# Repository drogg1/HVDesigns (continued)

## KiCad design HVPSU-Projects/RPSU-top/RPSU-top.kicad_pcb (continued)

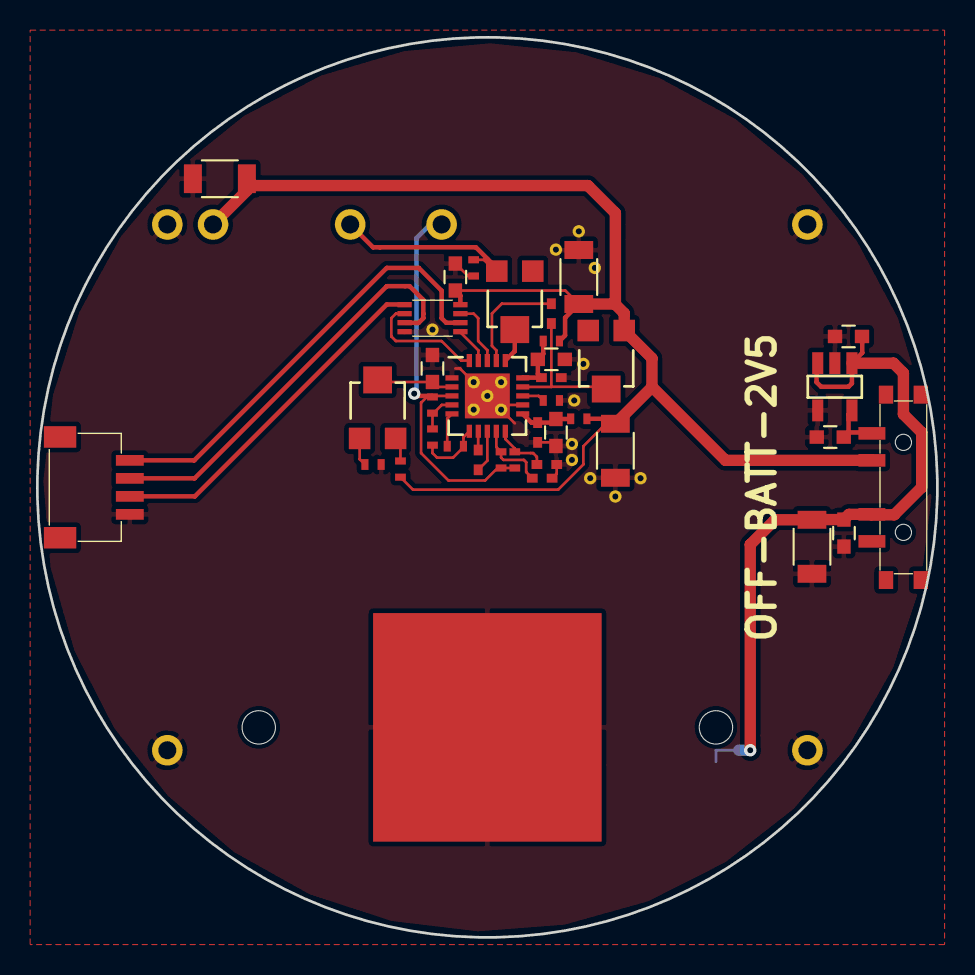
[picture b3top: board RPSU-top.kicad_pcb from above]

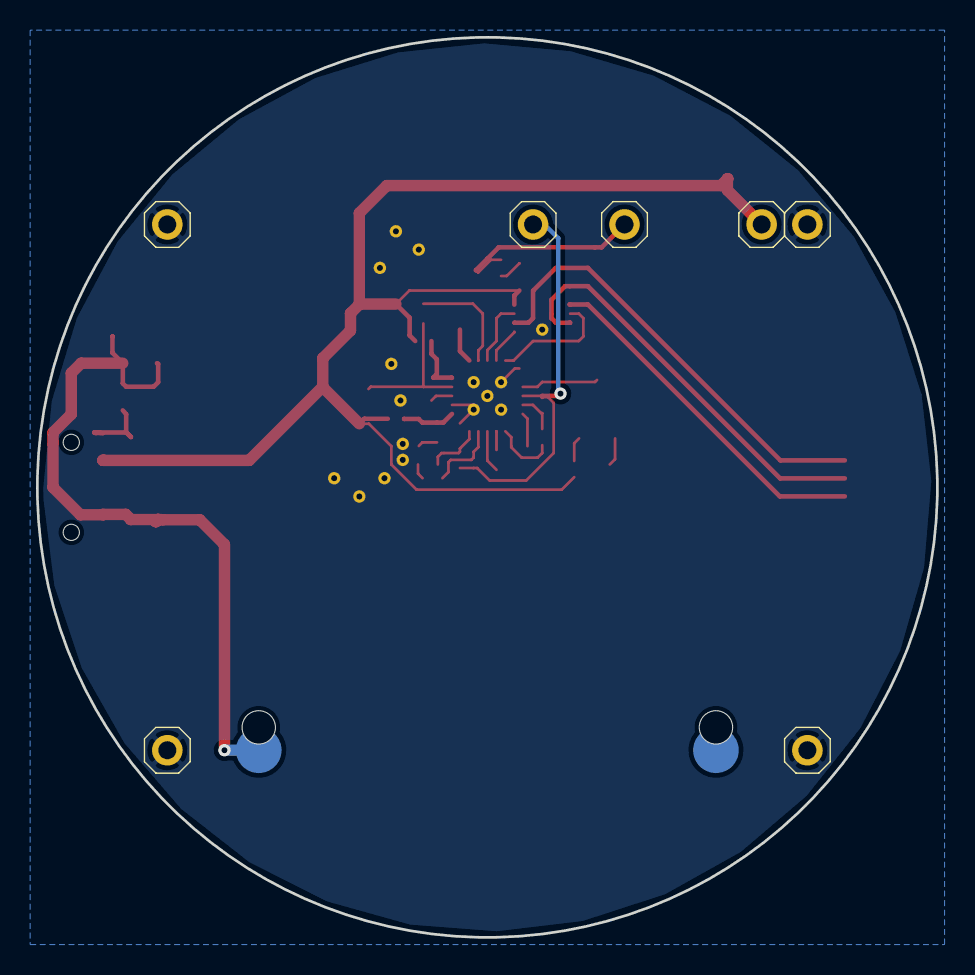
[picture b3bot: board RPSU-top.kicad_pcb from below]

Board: 2 copper layers, 50.0 x 50.0 mm, 44 parts (7 on the bottom side), 28 nets.

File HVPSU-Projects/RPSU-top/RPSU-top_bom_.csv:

Component,Description,Part,References,Value,Footprint,Quantity Per PCB,Datasheet
1,,Battery,BT1,Battery,KEY1027-ND-rev2,1,
2,Unpolarized capacitor,C_Small,C52 C54 C56 C58,0.1uF,C_0402_NoSilk,4,
3,Unpolarized capacitor,C_Small,C1 C63 C64 C65,10uF,C_1206,4,
4,Unpolarized capacitor,C_Small,C57,1nF,C_0402_NoSilk,1,
5,Unpolarized capacitor,C_Small,C50 C51 C53 C59 C60 C61 C62,1uF,C_0603,7,
6,Unpolarized capacitor,C_Small,C55,3.3nF,C_0402_NoSilk,1,
7,Connector 01x01,CONN_01X01,P2 P3 P4 P5 P6 P7 P8,CONN_01X01,PHS1x01_Pitch2.54mm_1D1.7P,7,
8,Connector 01x04,CONN_01X04,P1,CONN_01X04,SM04B-SRSS-TB(LF)(SN),1,
9,Resistor,R,R16 R17,10,R_0402_NoSilk,2,
10,Resistor,R,R1 R18 R19 R20 R22 R23,1M,R_0402_NoSilk,6,
11,Resistor,R,R15,2M,R_0402_NoSilk,1,
12,Resistor,R,R21,33M,R_0402_NoSilk,1,
13,Resistor,R,R14,560k,R_0402_NoSilk,1,
14,,POT-RESCUE-RPSU-top,RV1,1M,EVM3Y-POT,1,
15,,POT-RESCUE-RPSU-top,RV2 RV3,20k,EVM3Y-POT,2,
16,"3 position switch, SP3T",SP3T,SW1,SP3T,PCM13SMTR,1,
17,,SN74AUP3G17,U2,SN74AUP3G17,8-VFSOP,1,
18,,TPS78225DDCR,U3,TPS78225DDCR,TSOT-23-5,1,
19,,switch_ic4/5,U1,switch_ic4/5,QFN-20-1EP_4x4mm_Pitch0.5mm,1,





Component Groups:,19
Component Count:,44
Fitted Components:,44
Number of PCBs:,1
Total components:,44
Schematic Version:,
Schematic Date:,
BoM Date:,1/29/2019 10:01:43 PM
Schematic Source:,C:/Users/User/Google Drive/IC Research/Clean HV Designs/HVPSU-Projects/RPSU-top/RPSU-top.sch
KiCad Version:,Eeschema 4.0.2-stable

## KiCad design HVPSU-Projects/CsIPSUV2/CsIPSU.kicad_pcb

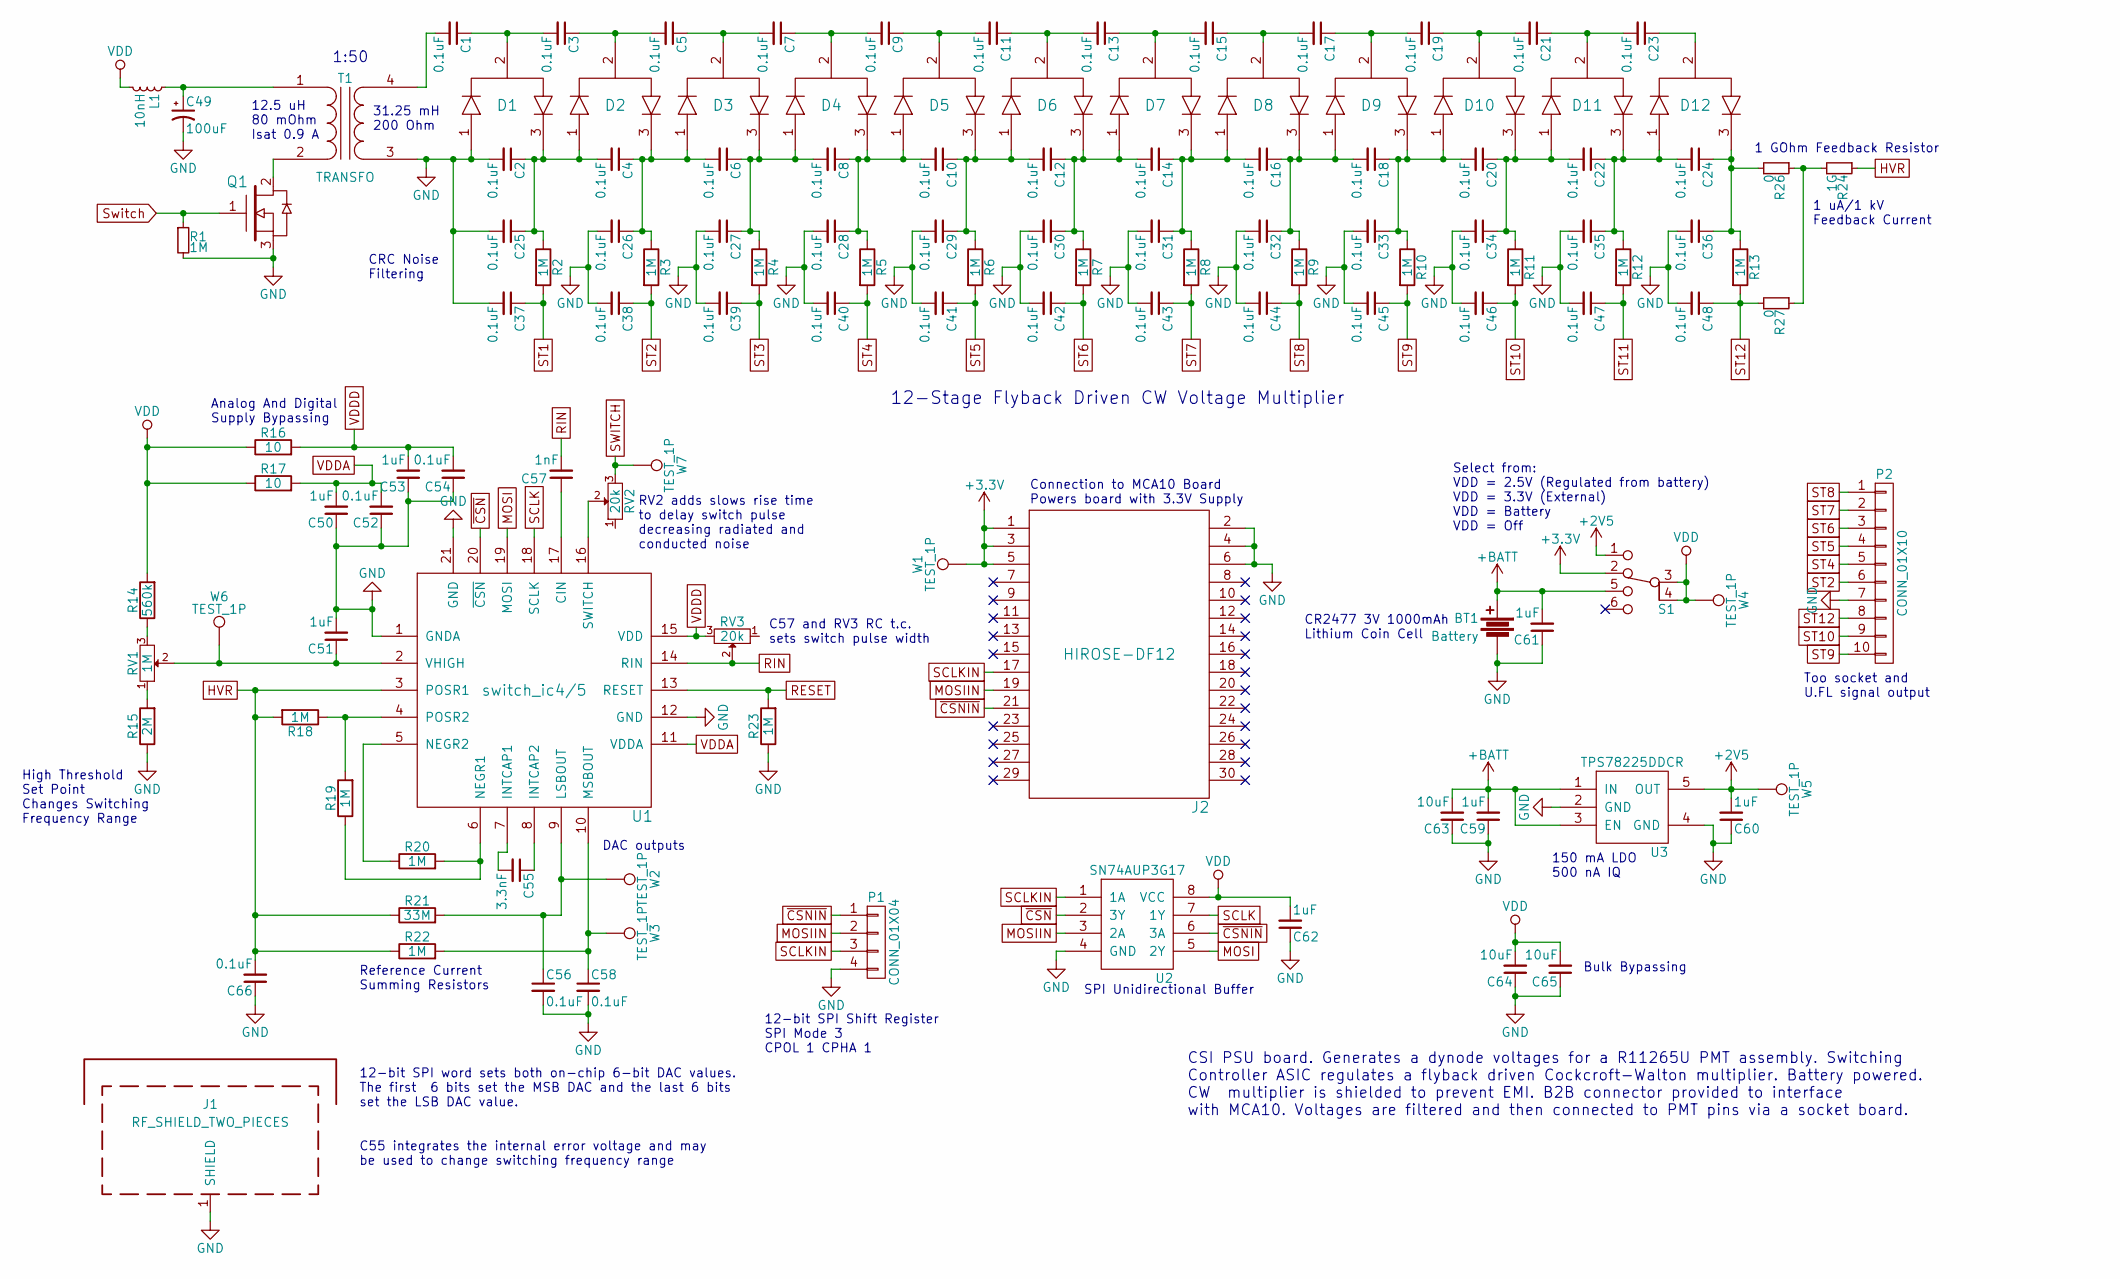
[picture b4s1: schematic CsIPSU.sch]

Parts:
BT1: Battery; KEY1027-ND
C1, C2, C3, C4, C5, C6, C7, C8, C9, C10, C11, C12, C13, C14, C15, C16, C17, C18, C19, C20, C21, C22, C23, C24: 0.1uF; HV-1206
C25, C26, C27, C28, C29, C30, C31, C32, C33, C34, C35, C36, C37, C38, C39, C40, C41, C42, C43, C44, C45, C46, C47, C48: 0.1uF; C_1812
C49: 100uF; CP_Tantalum_Case-C_EIA-6032-28_Reflow
C50, C51, C53, C59, C60, C61, C62: 1uF; C_0603
C52, C54, C56, C58, C66: 0.1uF; C_0402_NoSilk
C55: 3.3nF; C_0402_NoSilk
C57: 1nF; C_0402_NoSilk
C63, C64, C65: 10uF; C_1206
D1, D2, D3, D4, D5, D6, D7, D8, D9, D10, D11, D12: MMBD3004S; SOT23
J1: RF_SHIELD_TWO_PIECES; Laird_Technologies_BMI-S-205-F_38.10x25.40mm
J2: HIROSE-DF12; CheetahSocket
L1: 10nH; R_0402_NoSilk
P1: CONN_01X04; SM04B-SRSS-TB(LF)(SN)
P2: CONN_01X10; Pin_Header_Straight_1x10_Pitch2.54mm-narrowforhv
Q1: NMOS-DMG3420U; SOT23-mosfet
R1, R18, R19, R20, R22, R23: 1M; R_0402_NoSilk
R2, R3, R4, R5, R6, R7, R8, R9, R10, R11, R12, R13: 1M; R_0603
R14: 560k; R_0402_NoSilk
R15: 2M; R_0402_NoSilk
R16, R17: 10; R_0402_NoSilk
R21: 33M; R_0402_NoSilk
R24: 1G; R_2512_HandSoldering
R26, R27: 0; R_0603
RV1: 1M; EVM3Y-POT
RV2, RV3: 20k; EVM3Y-POT
S1: SP4T; CUS-14TB
T1: TRANSFO; LPR6235
U1: switch_ic4/5; QFN-20-1EP_4x4mm_Pitch0.5mm
U2: SN74AUP3G17; 8-VFSOP
U3: TPS78225DDCR; TSOT-23-5
W1: TEST_1P; Test_Point_Keystone_5019_Minature
W2, W3, W4, W5, W6, W7: TEST_1P; Measurement_Point_Round-SMD-Pad_Small

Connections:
+2V5: C60.2, S1.1, U3.5 (OUT), W5.1
+3V3: J2.1, J2.3, J2.5, S1.2, W1.1
+BATT: BT1.1, C59.2, C61.2, C63.2, S1.5, U3.1 (IN), U3.3 (EN)
GND: BT1.2, C2.2, C25.2, C26.2, C27.2, C28.2, C29.2, C30.2, C31.2, C32.2, C33.2, C34.2, C35.2, C36.2, C37.2, C38.2, C39.2, C40.2, C41.2, C42.2, C43.2, C44.2, C45.2, C46.2, C47.2, C48.2, C49.2, C50.1, C51.2, C52.1, C53.1, C54.1, C56.2, C58.2, C59.1, C60.1, C61.1, C62.1, C63.1, C64.1, C65.1, C66.1, D1.1, J1.1, J2.2, J2.4, J2.6, P1.4, P2.7, Q1.3 (S), R1.2, R15.1, R23.1, T1.3 (SA), U1.1 (GNDA), U1.12 (GND), U1.21 (GND), U2.4 (GND), U3.2 (GND), U3.4 (GND)
HVR: C66.2, R18.2, R21.1, R22.1, R24.1, U1.3 (POSR1)
MOSI: U1.19 (MOSI), U2.5 (2Y)
MOSIIN: J2.19, P1.2, U2.3 (2A)
unnamed: C1.1, C3.2, D1.2
unnamed: C1.2, T1.4 (SB)
unnamed: C2.1, C4.2, C25.1, D1.3, D2.1, R2.1
unnamed: C3.1, C5.2, D2.2
unnamed: C5.1, C7.2, D3.2
unnamed: C7.1, C9.2, D4.2
unnamed: C10.1, C12.2, C29.1, D5.3, D6.1, R6.1
unnamed: C8.1, C10.2, C28.1, D4.3, D5.1, R5.1
unnamed: C11.1, C13.2, D6.2
unnamed: C9.1, C11.2, D5.2
unnamed: C12.1, C14.2, C30.1, D6.3, D7.1, R7.1
unnamed: C13.1, C15.2, D7.2
unnamed: C14.1, C16.2, C31.1, D7.3, D8.1, R8.1
unnamed: C15.1, C17.2, D8.2
unnamed: C16.1, C18.2, C32.1, D8.3, D9.1, R9.1
unnamed: C17.1, C19.2, D9.2
unnamed: C18.1, C20.2, C33.1, D9.3, D10.1, R10.1
unnamed: C19.1, C21.2, D10.2
unnamed: C20.1, C22.2, C34.1, D10.3, D11.1, R11.1
unnamed: C21.1, C23.2, D11.2
unnamed: C22.1, C24.2, C35.1, D11.3, D12.1, R12.1
unnamed: C23.1, D12.2
unnamed: C24.1, C36.1, D12.3, R13.1, R26.2
unnamed: C4.1, C6.2, C26.1, D2.3, D3.1, R3.1
unnamed: C6.1, C8.2, C27.1, D3.3, D4.1, R4.1
unnamed: C49.1, L1.1, T1.1 (AA)
unnamed: C51.1, RV1.2, U1.2 (VHIGH), W6.1
unnamed: C55.1, U1.8 (INTCAP2)
unnamed: C55.2, U1.7 (INTCAP1)
unnamed: C56.1, R21.2, U1.9 (LSBOUT), W2.1
unnamed: C57.1, U1.17 (CIN)
unnamed: C58.1, R22.2, U1.10 (MSBOUT), W3.1
unnamed: Q1.2 (D), T1.2 (AB)
unnamed: R14.1, RV1.3
unnamed: R15.2, RV1.1
unnamed: R18.1, R19.2, U1.4 (POSR2)
unnamed: R19.1, R20.2, U1.6 (NEGR1)
unnamed: R20.1, U1.5 (NEGR2)
unnamed: R24.2, R26.1, R27.1
unnamed: RV2.2, U1.16 (SWITCH)
RESET: R23.2, U1.13 (RESET)
RIN: C57.2, RV3.2, U1.14 (RIN)
SCLK: U1.18 (SCLK), U2.7 (1Y)
SCLKIN: J2.17, P1.3, U2.1 (1A)
ST1: C37.1, R2.2
ST2: C38.1, P2.6, R3.2
ST3: C39.1, R4.2
ST4: C40.1, P2.5, R5.2
ST5: C41.1, P2.4, R6.2
ST6: C42.1, P2.3, R7.2
ST7: C43.1, P2.2, R8.2
ST8: C44.1, P2.1, R9.2
ST9: C45.1, P2.10, R10.2
ST10: C46.1, P2.9, R11.2
ST11: C47.1, R12.2
ST12: C48.1, P2.8, R13.2, R27.2
SWITCH: Q1.1 (G), R1.1, RV2.3, W7.1
VDD: C62.2, C64.2, C65.2, L1.2, R14.2, R16.1, R17.1, S1.3, S1.4, U2.8 (VCC), W4.1
VDDA: C50.2, C52.2, R17.2, U1.11 (VDDA)
VDDD: C53.2, C54.2, R16.2, RV3.3, U1.15 (VDD)
~CSN: U1.20 (~CSN), U2.2 (3Y)
~CSNIN: J2.21, P1.1, U2.6 (3A)

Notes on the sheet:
1:50
12.5 uH 80 mOhm Isat 0.9 A
31.25 mH 200 Ohm
Too socket and U.FL signal output
150 mA LDO 500 nA IQ
Bulk Bypassing
SPI Unidirectional Buffer
12-bit SPI Shift Register SPI Mode 3 CPOL 1 CPHA 1
DAC outputs
Reference Current Summing Resistors
High Threshold Set Point Changes Switching Frequency Range
Analog And Digital Supply Bypassing
Connection to MCA10 Board Powers board with 3.3V Supply
12-Stage Flyback Driven CW Voltage Multiplier
1 GOhm Feedback Resistor
1 uA/1 kV Feedback Current
CRC Noise Filtering
C57 and RV3 RC t.c. sets switch pulse width
RV2 adds slows rise time to delay switch pulse decreasing radiated and conducted noise
12-bit SPI word sets both on-chip 6-bit DAC values. The first 6 bits set the MSB DAC and the last 6 bits set the LSB DAC value.
C55 integrates the internal error voltage and may be used to change switching frequency range
Select from: VDD = 2.5V (Regulated from battery) VDD = 3.3V (External) VDD = Battery VDD = Off
CR2477 3V 1000mAh Lithium Coin Cell
CSI PSU board. Generates a dynode voltages for a R11265U PMT assembly. Switching Controller ASIC regulates a flyback driven Cockcroft-Walton multiplier. Battery powered. CW multiplier is shielded to prevent EMI. B2B connector provided to interface with MCA10. Voltages are filtered and then connecte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

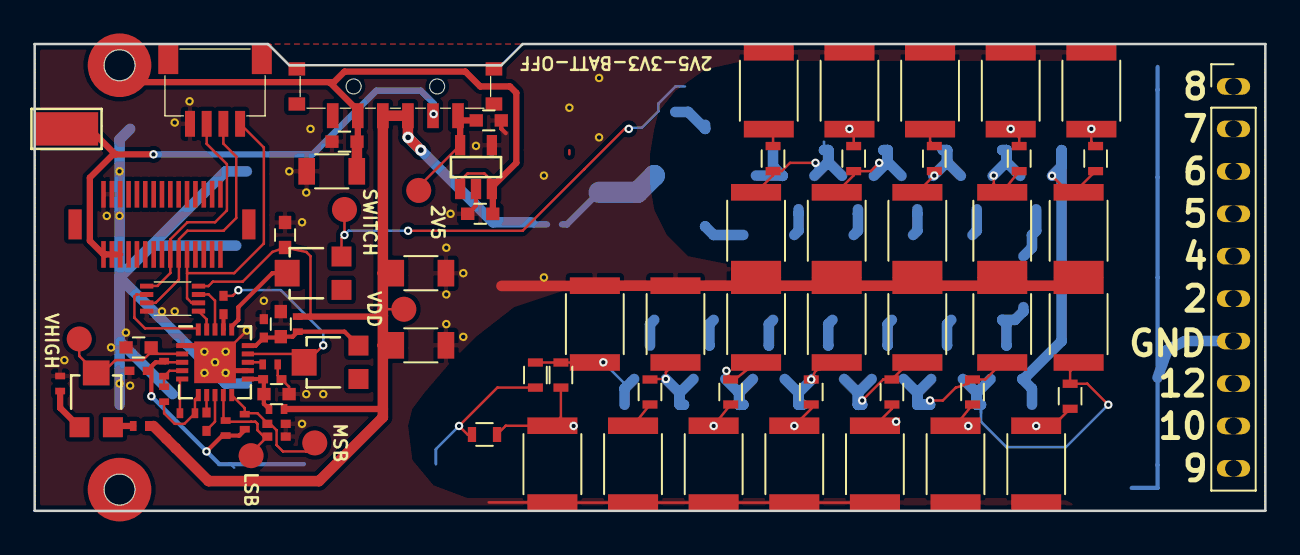
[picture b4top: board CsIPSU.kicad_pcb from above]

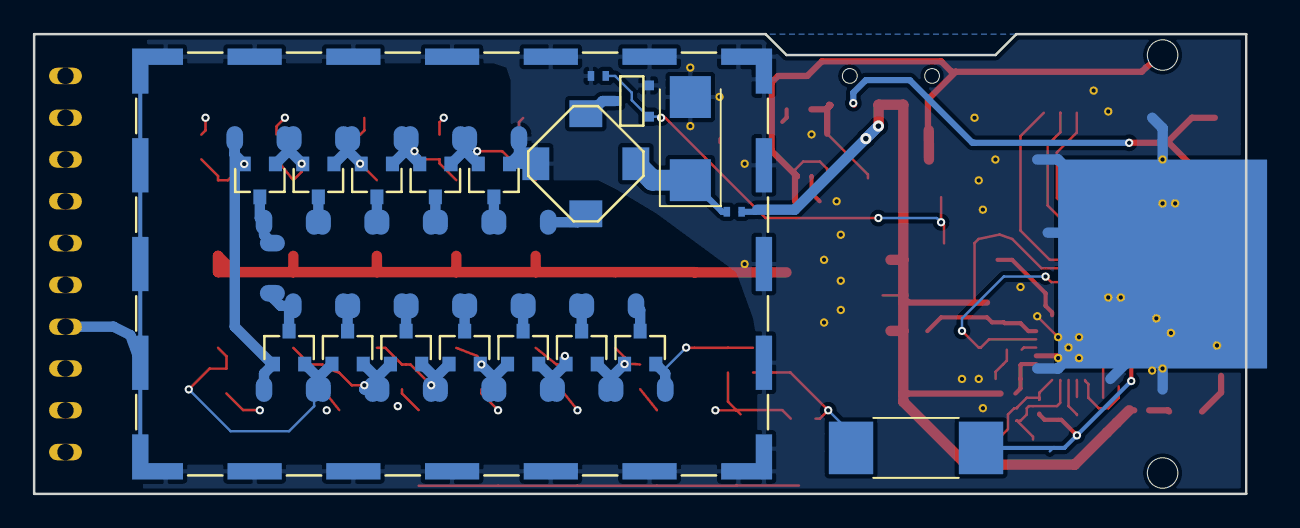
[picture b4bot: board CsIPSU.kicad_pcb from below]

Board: 4 copper layers, 73.7 x 27.9 mm, 126 parts (44 on the bottom side), 69 nets.

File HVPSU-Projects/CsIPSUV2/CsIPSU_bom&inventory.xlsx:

Component | Description | Part | References | Value | Footprint | Quantity Per PCB | Needed for | 8 | Inv |  | Need to Order | To Order | Notes | In order
CsIPSU
1 | Battery Clip | Battery | BT1 | Battery | KEY1027-ND | 1 | 8 |  | 7 |  | 1 | 1 |  | y
2 | Unpolarized capacitor | C_Small | C1 C2 C3 C4 C5 C6 C7 C8 C9 C10 C11 C12 C13 C14 C15 C16 C17 C18 C19 C20 C21 C22 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 | 0.1uF 250V X7R | HV-1206 | 24 | 192 |  | 158 |  | 34 | 50 |  | y
3 | Unpolarized capacitor | C_Small | C25 C26 C27 C28 C29 C30 C31 C32 C33 C34 C35 C36 C37 C38 C39 C40 C41 C42 C43 C44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 | 0.1uF | C_1812 | 25 | 200 |  | 0 |  | 200 | 225 |  | y
4 | Unpolarized capacitor | C_Small | C52 C54 C56 C58 C66 | 0.1uF | C_0402_NoSilk | 5 | 40 |  | 77 | 73(X7R 10V) | -37
5 | Polarised capacitor | CP1_Small | C49 | 100uF | CP_Tantalum_Case-C_EIA-6032-28_Reflow | 1 | 8 |  | 9 |  | -1
6 | Unpolarized capacitor | C_Small | C63 C64 C65 | 10uF | C_1206 | 3 | 24 |  | 14 |  | 10 | 25 |  | y
7 | Unpolarized capacitor | C_Small | C57 | 1nF | C_0402_NoSilk | 1 | 8 |  | 12 |  | -4
8 | Unpolarized capacitor | C_Small | C50 C51 C53 C59 C60 C61 C62 | 1uF | C_0603 | 7 | 56 |  | 84 |  | -28
9 | Unpolarized capacitor | C_Small | C55 | 3.3nF | C_0402_NoSilk | 1 | 8 |  | 54 |  | -46
10 | Dual Diode | MMBD3004S | D1 D2 D3 D4 D5 D6 D7 D8 D9 D10 D11 D12 | MMBD3004S | SOT23 | 12 | 96 |  | 142 |  | -46
11 | Socket Connector | HIROSE-DF12 | J2 | DF12B-30DS-0.5V(86) | CheetahSocket | 1 | 8 |  | 2 |  | 6 | 10 |  | y
12 | RF Shield | RF_SHIELD_TWO_PIECES | J1 | RF_SHIELD_TWO_PIECES | Laird_Technologies_BMI-S-205-F_38.10x25.40mm | 1 | 8 |  | 6 | 9(lids) | 2 | 1 |  | y
13 | Inductor | L_Small | L1 | 10nH | R_0402_NoSilk | 1 | 8 |  | 7 |  | 1 |  | swap with 10 ohm res
14 | Connector 01x04 | CONN_01X04 | P1 | CONN_01X04 | SM04B-SRSS-TB(LF)(SN) | 1 | 8 |  | 5 |  | 3 | 3 |  | y
15 | Connector 01x10 | CONN_01X10 | P2 | CONN_01X10 | Pin_Header_Straight_1x10_Pitch2.54mm-narrowforhv | 1 | 8 |  | 4 |  | 4 | 5 |  | y
16 | Switching MOSFET | NMOS-DMG3420U | Q1 | NMOS-DMG3420U | SOT23-mosfet | 1 | 8 |  | 144 |  | -136
17 | Resistor | R_Small | R26 R27 | 0 | R_0603 | 2 | 16 |  | 12 |  | 4 | 25 |  | y
18 | Resistor | R | R16 R17 | 10 | R_0402_NoSilk | 2 | 16 |  | 80 |  | -64
19 | Resistor | R_Small | R24 | 1G | R_2512_HandSoldering | 1 | 8 |  | 7 |  | 1 | 1 |  | y
20 | Resistor | R_Small | R1 R18 R19 R20 R22 R23 | 1M | R_0402_NoSilk | 6 | 48 |  | 181 |  | -133
21 | Resistor | R | R2 R3 R4 R5 R6 R7 R8 R9 R10 R11 R12 R13 | 1M | R_0603 | 12 | 96 |  | 90 |  | 6 | 100 |  | y
22 | Resistor | R | R15 | 2M | R_0402_NoSilk | 1 | 8 |  | 101 |  | -93
23 | Resistor | R | R21 | 33M | R_0402_NoSilk | 1 | 8 |  | 17 |  | -9
24 | Resistor | R | R14 | 560k | R_0402_NoSilk | 1 | 8 |  | 104 |  | -96
25 | High Threshold Adjust | POT-RESCUE-CsIPSU | RV1 | 1M | EVM3Y-POT | 1 | 8 |  | 10 |  | -2
26 | Pulse Width and Delay Adj | POT-RESCUE-CsIPSU | RV2 RV3 | 20k | EVM3Y-POT | 2 | 16 |  | 18 |  | -2
27 | Off-Battery-Exterior-2.5V | SP4T | S1 | SP4T | CUS-14TB | 1 | 8 |  | 3 |  | 5 | 2 |  | y
28 | Flyback Transformer | TRANSFO | T1 | TRANSFO | LPR6235 | 1 | 8 |  | 77 |  | -69
29 | SPI Buffer | SN74AUP3G17 | U2 | SN74AUP3G17 | 8-VFSOP | 1 | 8 |  | 6 |  | 2 | 2 |  | y
30 | 2.5V 150mA LDO | TPS78225DDCR | U3 | TPS78225DDCR | TSOT-23-5 | 1 | 8 |  | 6 |  | 2 | 2 |  | y
31 | Switching ASIC | switch_ic4/5 | U1 | switch_ic4/5 | QFN-20-1EP_4x4mm_Pitch0.5mm | 1 | 8 |  | 30 |  | -22
32 | point | TEST_1P | W2 W3 W4 W5 W6 W7 | TEST_1P | Measurement_Point_Round-SMD-Pad_Small | 6
Socket board
1 | Unpolarized capacitor | C_Small | C1 | 0.1uF | C_1812 | 1 | 2 |  | 0 |  | 2
2 | Unpolarized capacitor | C_Small | C2 | 0.1uF | C_0603_HandSoldering | 1 | 2 |  | 20 |  | -18
3 | Unpolarized capacitor | C_Small | C3 | 3.3nF | C_0603_HandSoldering | 1 | 2 |  | 20 |  | -18
4 |  | UFL-CONN | J1 | UFL-CONN | U.FL-R-SMT | 1 | 2 |  | 8 |  | -6
5 | Connector 01x10 | CONN_01X10 | P1 | CONN_01X10 | Pin_Header_Straight_1x10_Pitch2.54mm-narrowforhv | 1 | 2 |  | 160 |  | -158
6 | Resistor | R | R1 | 1M | R_0603_HandSoldering | 1 | 2 |  | 0 |  | 2 | 100 |  | y
7 | Resistor | R | R2 | 2M | R_0603_HandSoldering | 1 | 2 |  | 17 |  | -15
8 |  | R11265U-PMT-socket | U1 | R11265U-PMT-socket | R11265U-PMT-socket | 14 | 70 |  | 50 |  | 20 | 30 |  | y

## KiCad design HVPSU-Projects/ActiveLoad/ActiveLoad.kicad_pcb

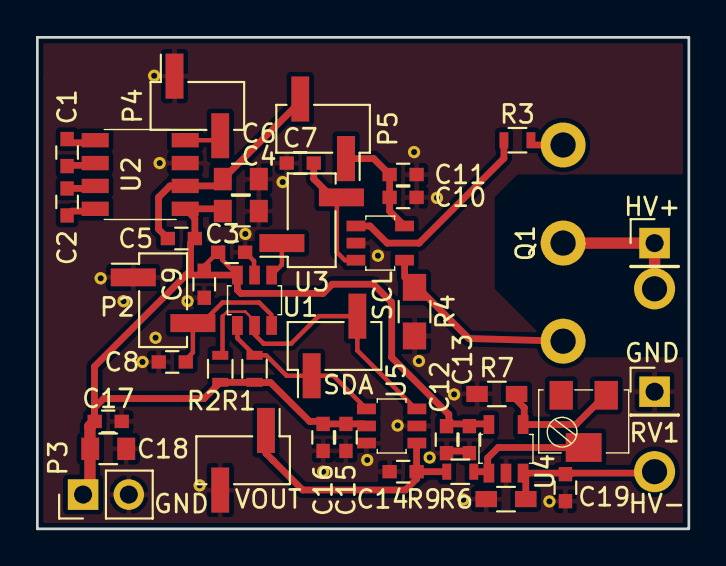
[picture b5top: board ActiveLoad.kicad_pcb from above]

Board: 2 copper layers, 36.2 x 27.3 mm, 44 parts (0 on the bottom side), 22 nets.

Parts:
C1, C2: 220nF; C_0603
C3, C9, C11, C16, C17: 10uF; C_0603
C4, C6, C18: 4.7uF; C_0805
C5: 100nF; C_0603
C7, C8, C10, C12, C14, C15, C19: 0.1uF; C_0603
C13: 1uF; C_0603
GND: GND; Pin_Header_Straight_1x01_Pitch2.54mm
HV+: HV+P; 677-millmax-pin-socket
HV-: HV+N; 677-millmax-pin-socket
P2: CONN_01X02; Pin_Header_Straight_1x02_Pitch2.54mm_SMD_Pin1Left
P3: CONN_01X02; Pin_Header_Straight_1x02_Pitch2.54mm
P4, P5: CONN_01X02; Pin_Header_Straight_1x02_Pitch2.54mm_SMD_Pin1Right
P6: HV+; Pin_Header_Straight_1x01_Pitch2.54mm
Q1: NDTL03N150C; TO-3P-3L
R1, R2: 700; R_0603
R3: 100; R_0603
R4: 100k; R_0805_HandSoldering
R6: 10M; R_0603_HandSoldering
R7: 10k; R_0603_HandSoldering
R9: 1k; R_0603
RV1: POT; PVG5A-10turnpot
SCL: CONN_01X02; Pin_Header_Straight_1x02_Pitch2.54mm_SMD_Pin1Right
SDA: CONN_01X02; Pin_Header_Straight_1x02_Pitch2.54mm_SMD_Pin1Left
U1: MCP4726; SOT-23-6
U2: ST662; SO-8
U3: OPA191; SOT-23-5
U4: LMP2231; SOT-23-5
U5: MCP3421; SOT-23-6
VOUT: CONN_01X02; Pin_Header_Straight_1x02_Pitch2.54mm_SMD_Pin1Left

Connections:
/SCL: R2.1, SDA.2, U1.5, U5.3
/SDA: R1.1, SDA.1, U1.4, U5.4
/VCP: C5.1, C6.2, P5.2, U2.6
/VDAC: SCL.1, U1.1
/VREF: C8.1, P2.2, U1.6
/VSET: C7.2, SCL.2, U3.3
GND: C3.1, C4.1, C6.1, C7.1, C8.2, C9.1, C10.1, C11.1, C12.1, C13.1, C14.1, C15.1, C16.1, C17.1, C18.1, C19.1, GND.1, P2.1, P3.2, P4.1, R4.2, R6.2, R7.1, U1.2, U2.7, U3.2, U4.2, U5.2, U5.6, VOUT.2
unnamed: C1.1, U2.2
unnamed: C1.2, U2.1
unnamed: C2.1, U2.4
unnamed: C2.2, U2.3
unnamed: C14.2, R9.1, U5.1, VOUT.1
unnamed: C19.2, HV-.1, R6.1, U4.3
unnamed: P4.2, U2.8
unnamed: HV+.1, P6.1, Q1.2
unnamed: Q1.1, R3.2
unnamed: Q1.3, R4.1, U3.4
unnamed: R3.1, U3.1
unnamed: R7.2, RV1.1, U4.4
unnamed: R9.2, RV1.2, U4.1
VCC: C10.2, C11.2, P5.1, U3.5
VDD: C3.2, C4.2, C5.2, C9.2, C12.2, C13.2, C15.2, C16.2, C17.2, C18.2, P3.1, R1.2, R2.2, U1.3, U2.5, U4.5, U5.5

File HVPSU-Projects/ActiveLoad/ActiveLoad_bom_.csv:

Component,Description,Part,References,Value,Footprint,Quantity Per PCB,Datasheet
1,Unpolarized capacitor,C_Small,C5 C7 C8 C10 C12 C14 C15 C19,100nF,C_0603,8,
2,Unpolarized capacitor,C_Small,C3 C9 C11 C16 C17,10uF,C_0603,5,
3,Unpolarized capacitor,C_Small,C13,1uF,C_0603,1,
4,Unpolarized capacitor,C_Small,C1 C2,220nF,C_0603,2,
5,Unpolarized capacitor,C_Small,C4 C6 C18,4.7uF,C_0805,3,
6,Connector 01x02,CONN_01X02,P1 P4 P5,CONN_01X02,Pin_Header_Straight_1x02_Pitch2.54mm_SMD_Pin1Right,3,
7,Connector 01x02,CONN_01X02,P2 P7 P8,CONN_01X02,Pin_Header_Straight_1x02_Pitch2.54mm_SMD_Pin1Left,3,
8,Connector 01x02,CONN_01X02,P3,CONN_01X02,Pin_Header_Straight_1x02_Pitch2.54mm,1,
9,Connector 01x01,CONN_01X01,P11,GND,Pin_Header_Straight_1x01_Pitch2.54mm,1,
10,Connector 01x01,CONN_01X01,P6,HV+,Pin_Header_Straight_1x01_Pitch2.54mm,1,
11,Connector 01x01,CONN_01X01,P10,HV+N,677-millmax-pin-socket,1,
12,Connector 01x01,CONN_01X01,P9,HV+P,677-millmax-pin-socket,1,
13,"1500V Vds, N-Channel MOSFET, TO-3P-3L",NDTL03N150C,Q1,NDTL03N150C,TO-3P-3L,1,http://www.onsemi.com/pub/Collateral/NDTL03N150C-D.PDF
14,Resistor,R_Small,R3,100,R_0603,1,
15,Resistor,R_Small,R4,100k,R_0805_HandSoldering,1,
16,Resistor,R_Small,R6,10M,R_0603_HandSoldering,1,
17,Resistor,R_Small,R7,10k,R_0603_HandSoldering,1,
18,Resistor,R_Small,R9,1k,R_0603,1,
19,Resistor,R_Small,R1 R2,2.2k,R_0603,2,
20,,POT-RESCUE-ActiveLoad,RV1,POT,PVG5A-10turnpot,1,
21,,LMP2231,U4,LMP2231,SOT-23-5,1,
22,,MCP3421,U5,MCP3421,SOT-23-6,1,
23,,MCP4726,U1,MCP4726,SOT-23-6,1,
24,,OPA191,U3,OPA191,SOT-23-5,1,
25,,ST662,U2,ST662,SO-8,1,
,,,,,,,
,,,,,,,
,,,,,,,
,,,,,,,
,,,,,,,
Component Groups:,25,,,,,,
Component Count:,44,,,,,,
Fitted Components:,44,,,,,,
Number of PCBs:,1,,,,,,
Total components:,44,,,,,,
Schematic Version:,,,,,,,
Schematic Date:,,,,,,,
BoM Date:,1/29/2019 22:07,,,,,,
Schematic Source:,C:/Users/User/Google Drive/IC Research/Clean HV Designs/HVPSU-Projects/ActiveLoad/ActiveLoad.sch,,,,,,
KiCad Version:,Eeschema 4.0.2-stable,,,,,,

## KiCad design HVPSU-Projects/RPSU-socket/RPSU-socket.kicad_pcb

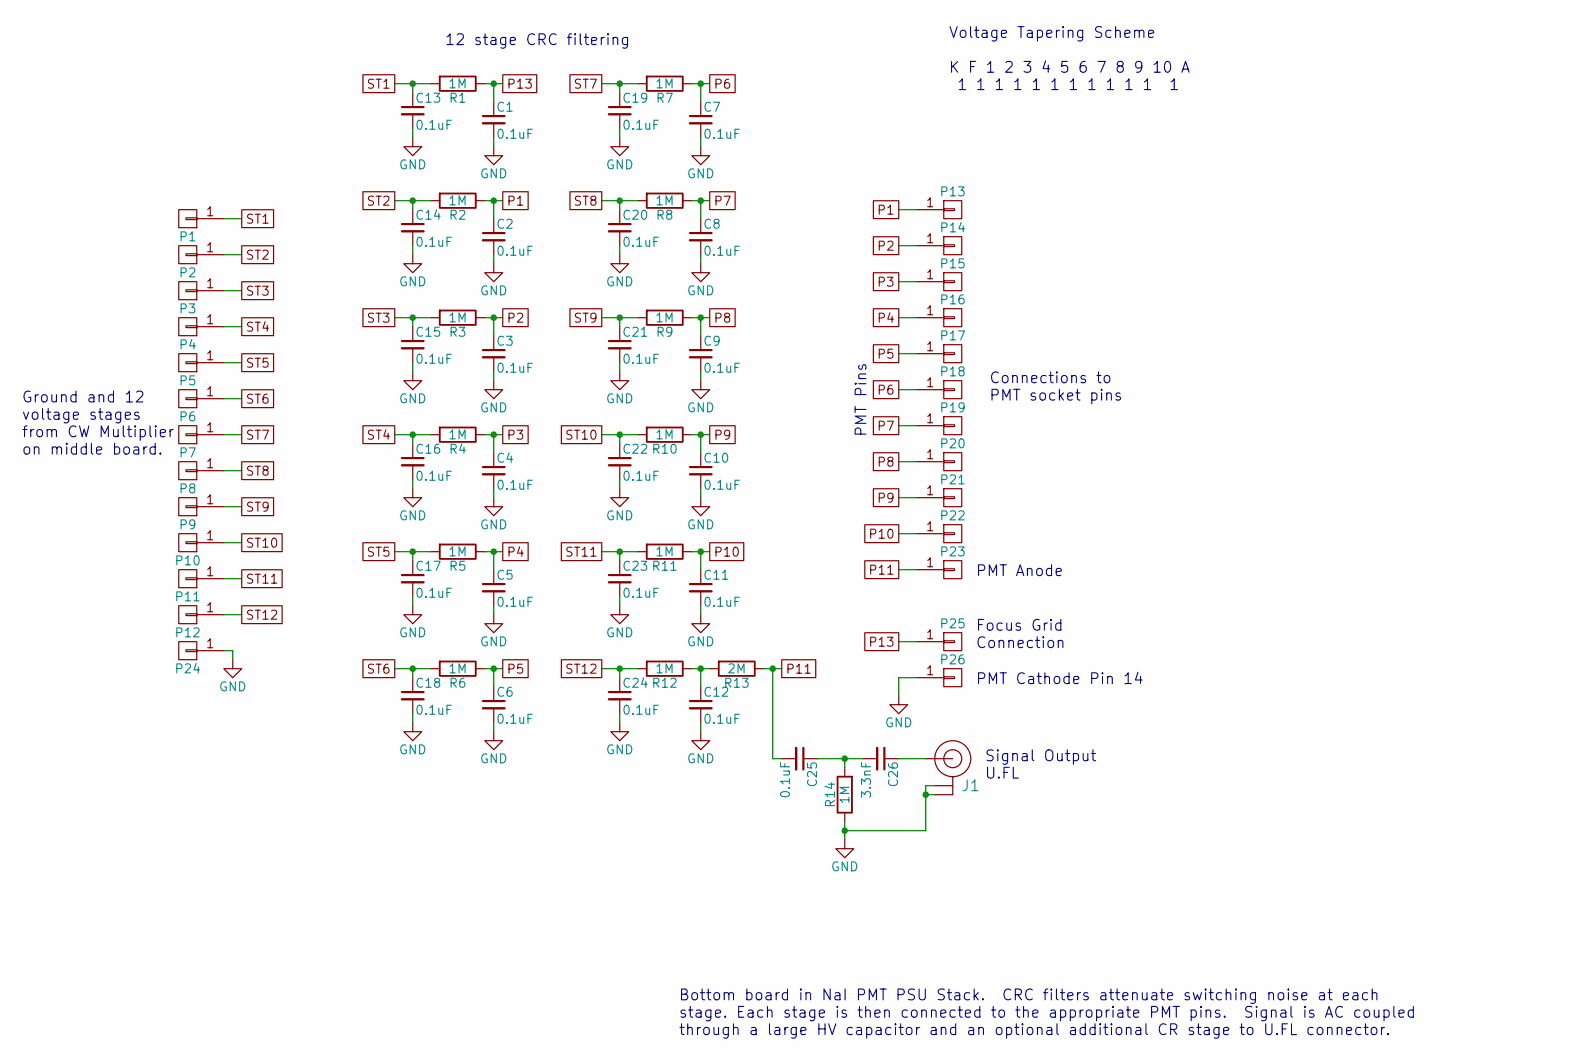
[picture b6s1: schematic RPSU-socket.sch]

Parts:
C1, C2, C3, C4, C5, C6, C7, C8, C9, C10, C11, C12, C13, C14, C15, C16, C17, C18, C19, C20, C21, C22, C23, C24, C25: 0.1uF; C_1812_sideways
C26: 3.3nF; C_0603_HandSoldering
J1: UFL-CONN; U.FL-R-SMT
P1, P2, P3, P4, P5, P6, P7, P8, P9, P10, P11, P12, P13, P14, P15, P16, P17, P18, P19, P20, P21, P22, P23, P24, P25, P26: 1; Pin_Header_Straight_1x01
R1, R2, R3, R4, R5, R6, R7, R8, R9, R10, R11, R12, R14: 1M; R_0603
R13: 2M; R_0603

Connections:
GND: C1.2, C2.2, C3.2, C4.2, C5.2, C6.2, C7.2, C8.2, C9.2, C10.2, C11.2, C12.2, C13.2, C14.2, C15.2, C16.2, C17.2, C18.2, C19.2, C20.2, C21.2, C22.2, C23.2, C24.2, J1.2 (GND1), J1.3 (GND2), P24.1, P26.1, R14.1
unnamed: C12.1, R12.1, R13.2
unnamed: C25.1, C26.2, R14.2
unnamed: C26.1, J1.1 (RF)
P1: C2.1, P13.1, R2.1
P2: C3.1, P14.1, R3.1
P3: C4.1, P15.1, R4.1
P4: C5.1, P16.1, R5.1
P5: C6.1, P17.1, R6.1
P6: C7.1, P18.1, R7.1
P7: C8.1, P19.1, R8.1
P8: C9.1, P20.1, R9.1
P9: C10.1, P21.1, R10.1
P10: C11.1, P22.1, R11.1
P11: C25.2, P23.1, R13.1
P13: C1.1, P25.1, R1.1
ST1: C13.1, P1.1, R1.2
ST2: C14.1, P2.1, R2.2
ST3: C15.1, P3.1, R3.2
ST4: C16.1, P4.1, R4.2
ST5: C17.1, P5.1, R5.2
ST6: C18.1, P6.1, R6.2
ST7: C19.1, P7.1, R7.2
ST8: C20.1, P8.1, R8.2
ST9: C21.1, P9.1, R9.2
ST10: C22.1, P10.1, R10.2
ST11: C23.1, P11.1, R11.2
ST12: C24.1, P12.1, R12.2

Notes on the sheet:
Bottom board in NaI PMT PSU Stack. CRC filters attenuate switching noise at each stage. Each stage is then connected to the appropriate PMT pins. Signal is AC coupled through a large HV capacitor and an optional additional CR stage to U.FL connector.
Ground and 12 voltage stages from CW Multiplier on middle board.
12 stage CRC filtering
Connections to PMT socket pins
Focus Grid Connection
Signal Output U.FL
PMT Pins
PMT Cathode Pin 14
Voltage Tapering Scheme K F 1 2 3 4 5 6 7 8 9 10 A 1 1 1 1 1 1 1 1 1 1 1 1
PMT Anode

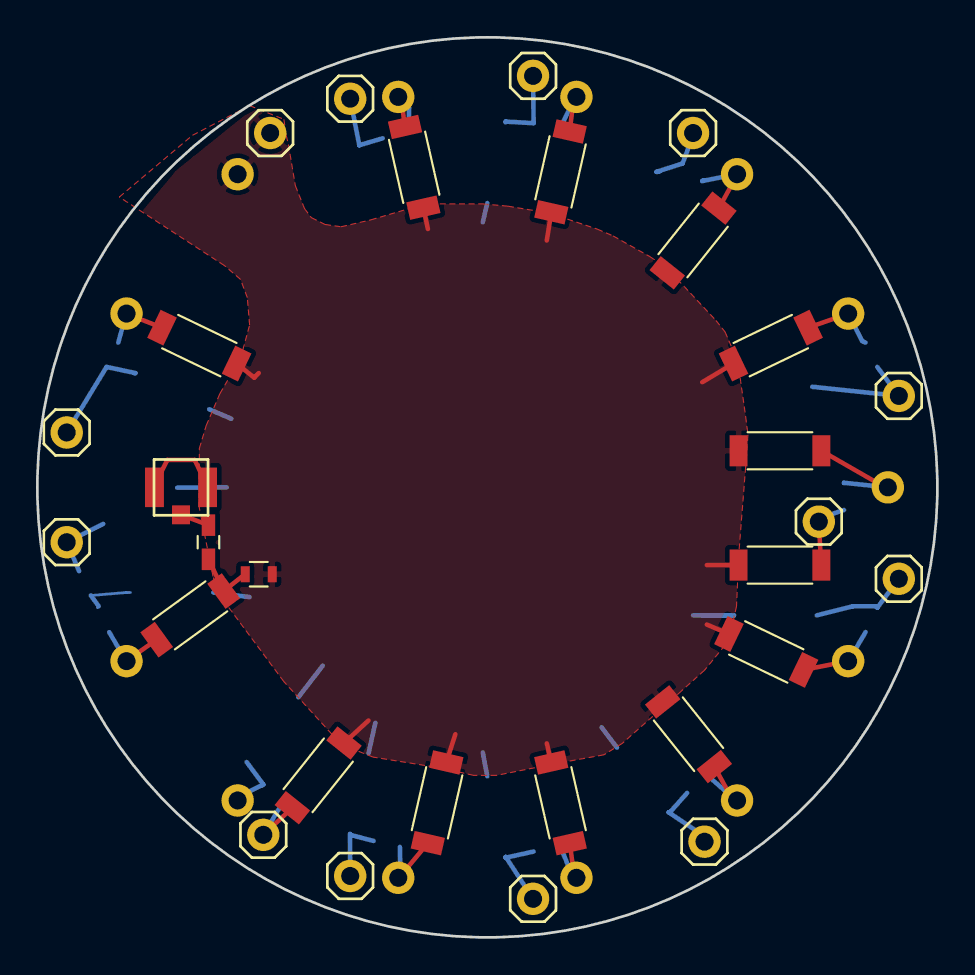
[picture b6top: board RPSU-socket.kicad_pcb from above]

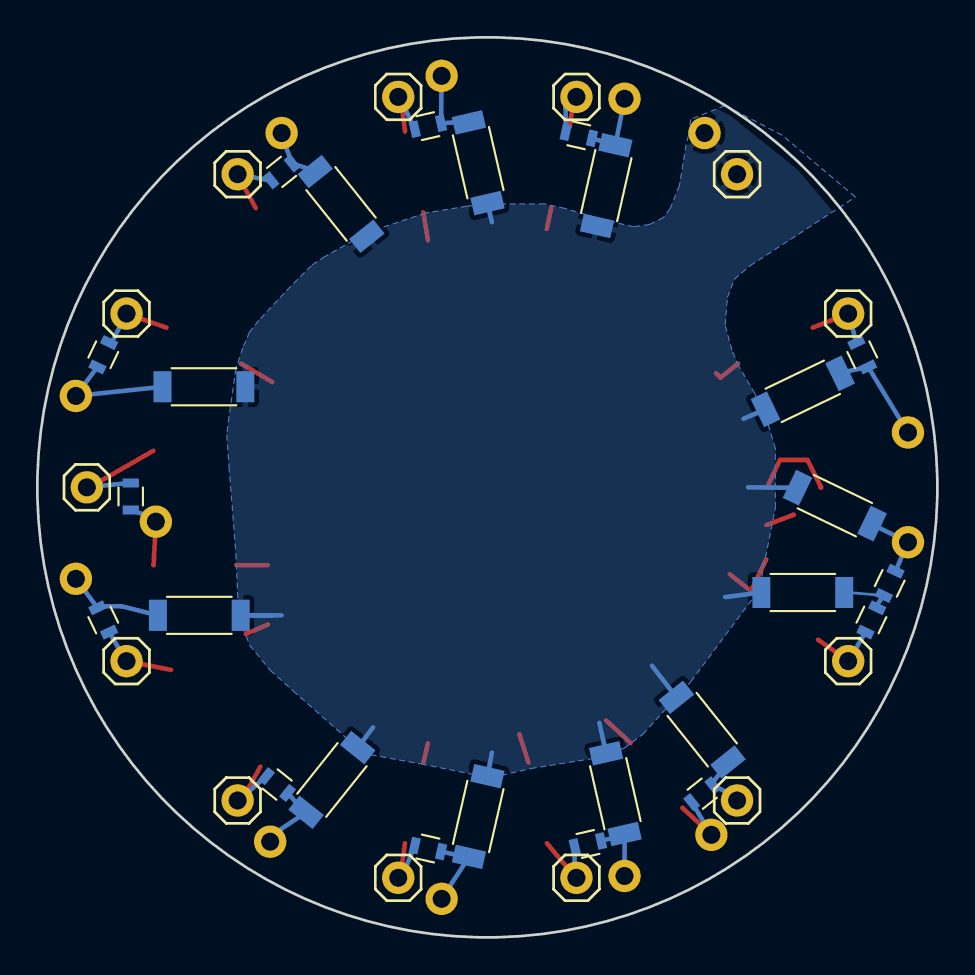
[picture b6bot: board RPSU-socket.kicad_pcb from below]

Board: 2 copper layers, 50.0 x 50.0 mm, 67 parts (38 on the bottom side), 28 nets.

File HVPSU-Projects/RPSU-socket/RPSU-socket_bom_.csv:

Component,Description,Part,References,Value,Footprint,Quantity Per PCB,Datasheet,order/hve
1,Unpolarized capacitor,C_Small,C1 C2 C3 C4 C5 C6 C7 C8 C9 C10 C11 C12 C13 C14 C15 C16 C17 C18 C19 C20 C21 C22 C23 C24 C25,0.1uF,C_1812_sideways,25,,y
2,Unpolarized capacitor,C_Small,C26,3.3nF,C_0603_HandSoldering,1,,y
3,,UFL-CONN,J1,UFL-CONN,U.FL-R-SMT,1,,y
4,Connector 01x01,CONN_01X01,P1 P2 P3 P4 P5 P6 P7 P8 P9 P10 P11 P12 P13 P14 P15 P16 P17 P18 P19 P20 P21 P22 P23 P24 P25 P26,1,Pin_Header_Straight_1x01,26,,y
5,Resistor,R,R1 R2 R3 R4 R5 R6 R7 R8 R9 R10 R11 R12 R14,1M,R_0603,13,,y
6,Resistor,R,R13,2M,R_0603,1,,y
,,,,,,,,
,,,,,,,,
,,,,,,,,
,,,,,,,,
,,,,,,,,
Component Groups:,6,,,,,,,
Component Count:,67,,,,,,,
Fitted Components:,67,,,,,,,
Number of PCBs:,1,,,,,,,
Total components:,67,,,,,,,
Schematic Version:,,,,,,,,
Schematic Date:,,,,,,,,
BoM Date:,2/6/2019 0:20,,,,,,,
Schematic Source:,C:/Users/User/Google Drive/IC Research/Clean HV Designs/HVPSU-Projects/RPSU-socket/RPSU-socket.sch,,,,,,,
KiCad Version:,Eeschema 4.0.2-stable,,,,,,,

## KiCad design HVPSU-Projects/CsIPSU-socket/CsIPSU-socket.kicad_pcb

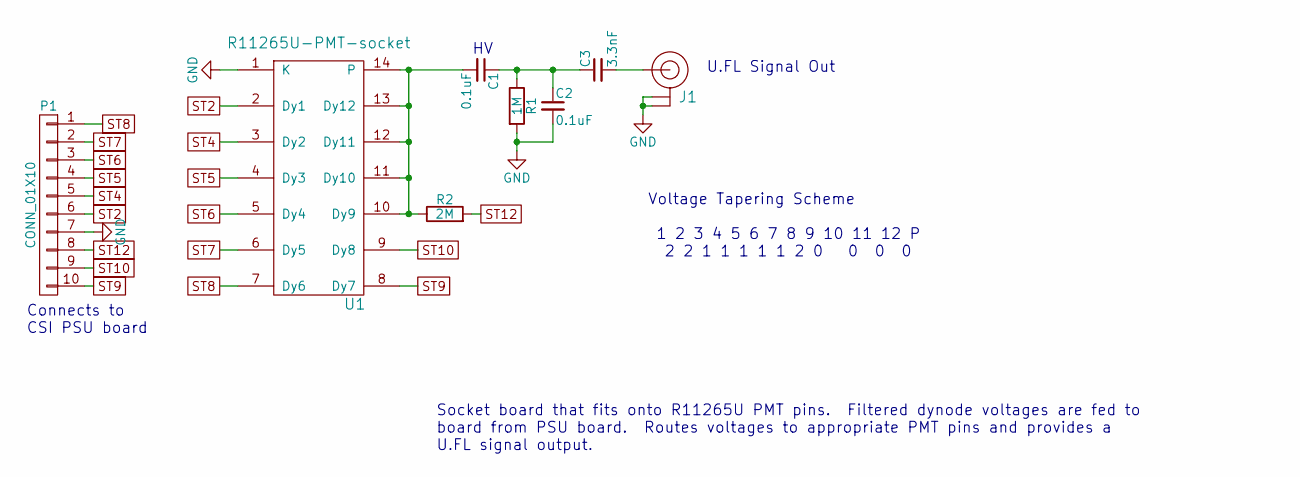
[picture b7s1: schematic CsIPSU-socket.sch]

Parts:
C1: 0.1uF; C_1812
C2: 0.1uF; C_0603_HandSoldering
C3: 3.3nF; C_0603_HandSoldering
J1: UFL-CONN; U.FL-R-SMT
P1: CONN_01X10; Pin_Header_Straight_1x10_Pitch2.54mm-narrowforhv
R1: 1M; R_0603_HandSoldering
R2: 2M; R_0603_HandSoldering
U1: R11265U-PMT-socket

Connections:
GND: C2.2, J1.2 (GND1), J1.3 (GND2), P1.7, R1.2, U1.1 (K)
unnamed: C1.1, C2.1, C3.1, R1.1
unnamed: C1.2, R2.1, U1.10 (Dy9), U1.11 (Dy10), U1.12 (Dy11), U1.13 (Dy12), U1.14
unnamed: C3.2, J1.1 (RF)
ST2: P1.6, U1.2 (Dy1)
ST4: P1.5, U1.3 (Dy2)
ST5: P1.4, U1.4 (Dy3)
ST6: P1.3, U1.5 (Dy4)
ST7: P1.2, U1.6 (Dy5)
ST8: P1.1, U1.7 (Dy6)
ST9: P1.10, U1.8 (Dy7)
ST10: P1.9, U1.9 (Dy8)
ST12: P1.8, R2.2

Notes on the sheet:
Connects to CSI PSU board
U.FL Signal Out
Socket board that fits onto R11265U PMT pins. Filtered dynode voltages are fed to board from PSU board. Routes voltages to appropriate PMT pins and provides a U.FL signal output.
Voltage Tapering Scheme 1 2 3 4 5 6 7 8 9 10 11 12 P 2 2 1 1 1 1 1 2 0 0 0 0

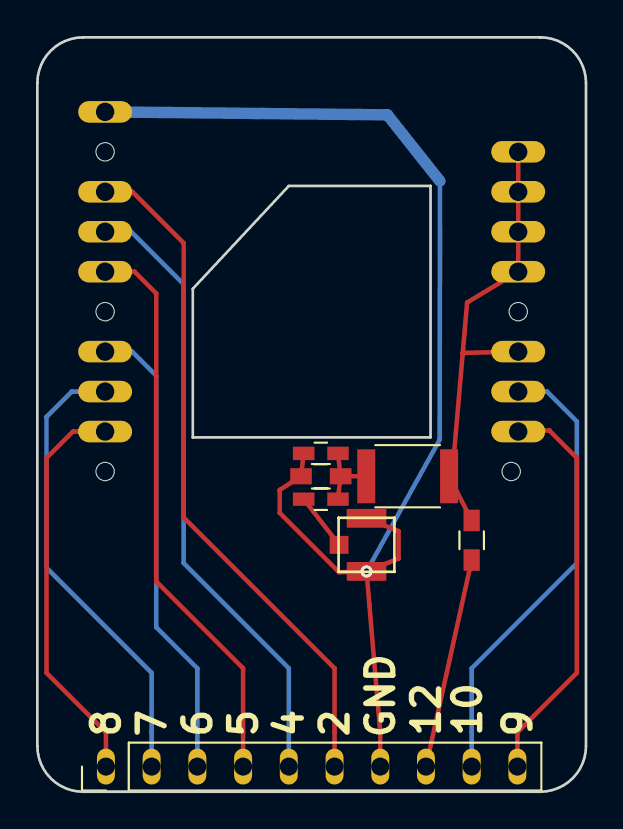
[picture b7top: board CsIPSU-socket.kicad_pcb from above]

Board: 2 copper layers, 30.5 x 41.9 mm, 8 parts (0 on the bottom side), 13 nets.

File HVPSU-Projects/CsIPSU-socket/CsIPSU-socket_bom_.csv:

Component,Description,Part,References,Value,Footprint,Quantity Per PCB,Datasheet
1,Unpolarized capacitor,C_Small,C1,0.1uF,C_1812,1,
2,Unpolarized capacitor,C_Small,C2,0.1uF,C_0603_HandSoldering,1,
3,Unpolarized capacitor,C_Small,C3,3.3nF,C_0603_HandSoldering,1,
4,,UFL-CONN,J1,UFL-CONN,U.FL-R-SMT,1,
5,Connector 01x10,CONN_01X10,P1,CONN_01X10,Pin_Header_Straight_1x10_Pitch2.54mm-narrowforhv,1,
6,Resistor,R,R1,1M,R_0603_HandSoldering,1,
7,Resistor,R,R2,2M,R_0603_HandSoldering,1,
8,,R11265U-PMT-socket,U1,R11265U-PMT-socket,R11265U-PMT-socket,1,





Component Groups:,8
Component Count:,8
Fitted Components:,8
Number of PCBs:,1
Total components:,8
Schematic Version:,
Schematic Date:,
BoM Date:,2/4/2019 10:07:08 PM
Schematic Source:,C:/Users/User/Google Drive/IC Research/Clean HV Designs/HVPSU-Projects/CsIPSU-socket/CsIPSU-socket.sch
KiCad Version:,Eeschema 4.0.2-stable

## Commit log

2019-03-03 latest
2019-03-03 Added CCS test code for HV supplies.
2019-03-04 Working on the test code. Shifting data into the DAC I believe works. Need to test the I2C code needed to communicate with the HV Measurement ADC.
2019-03-25 Latest code. Should work to test supplies and output HV anode voltage.
